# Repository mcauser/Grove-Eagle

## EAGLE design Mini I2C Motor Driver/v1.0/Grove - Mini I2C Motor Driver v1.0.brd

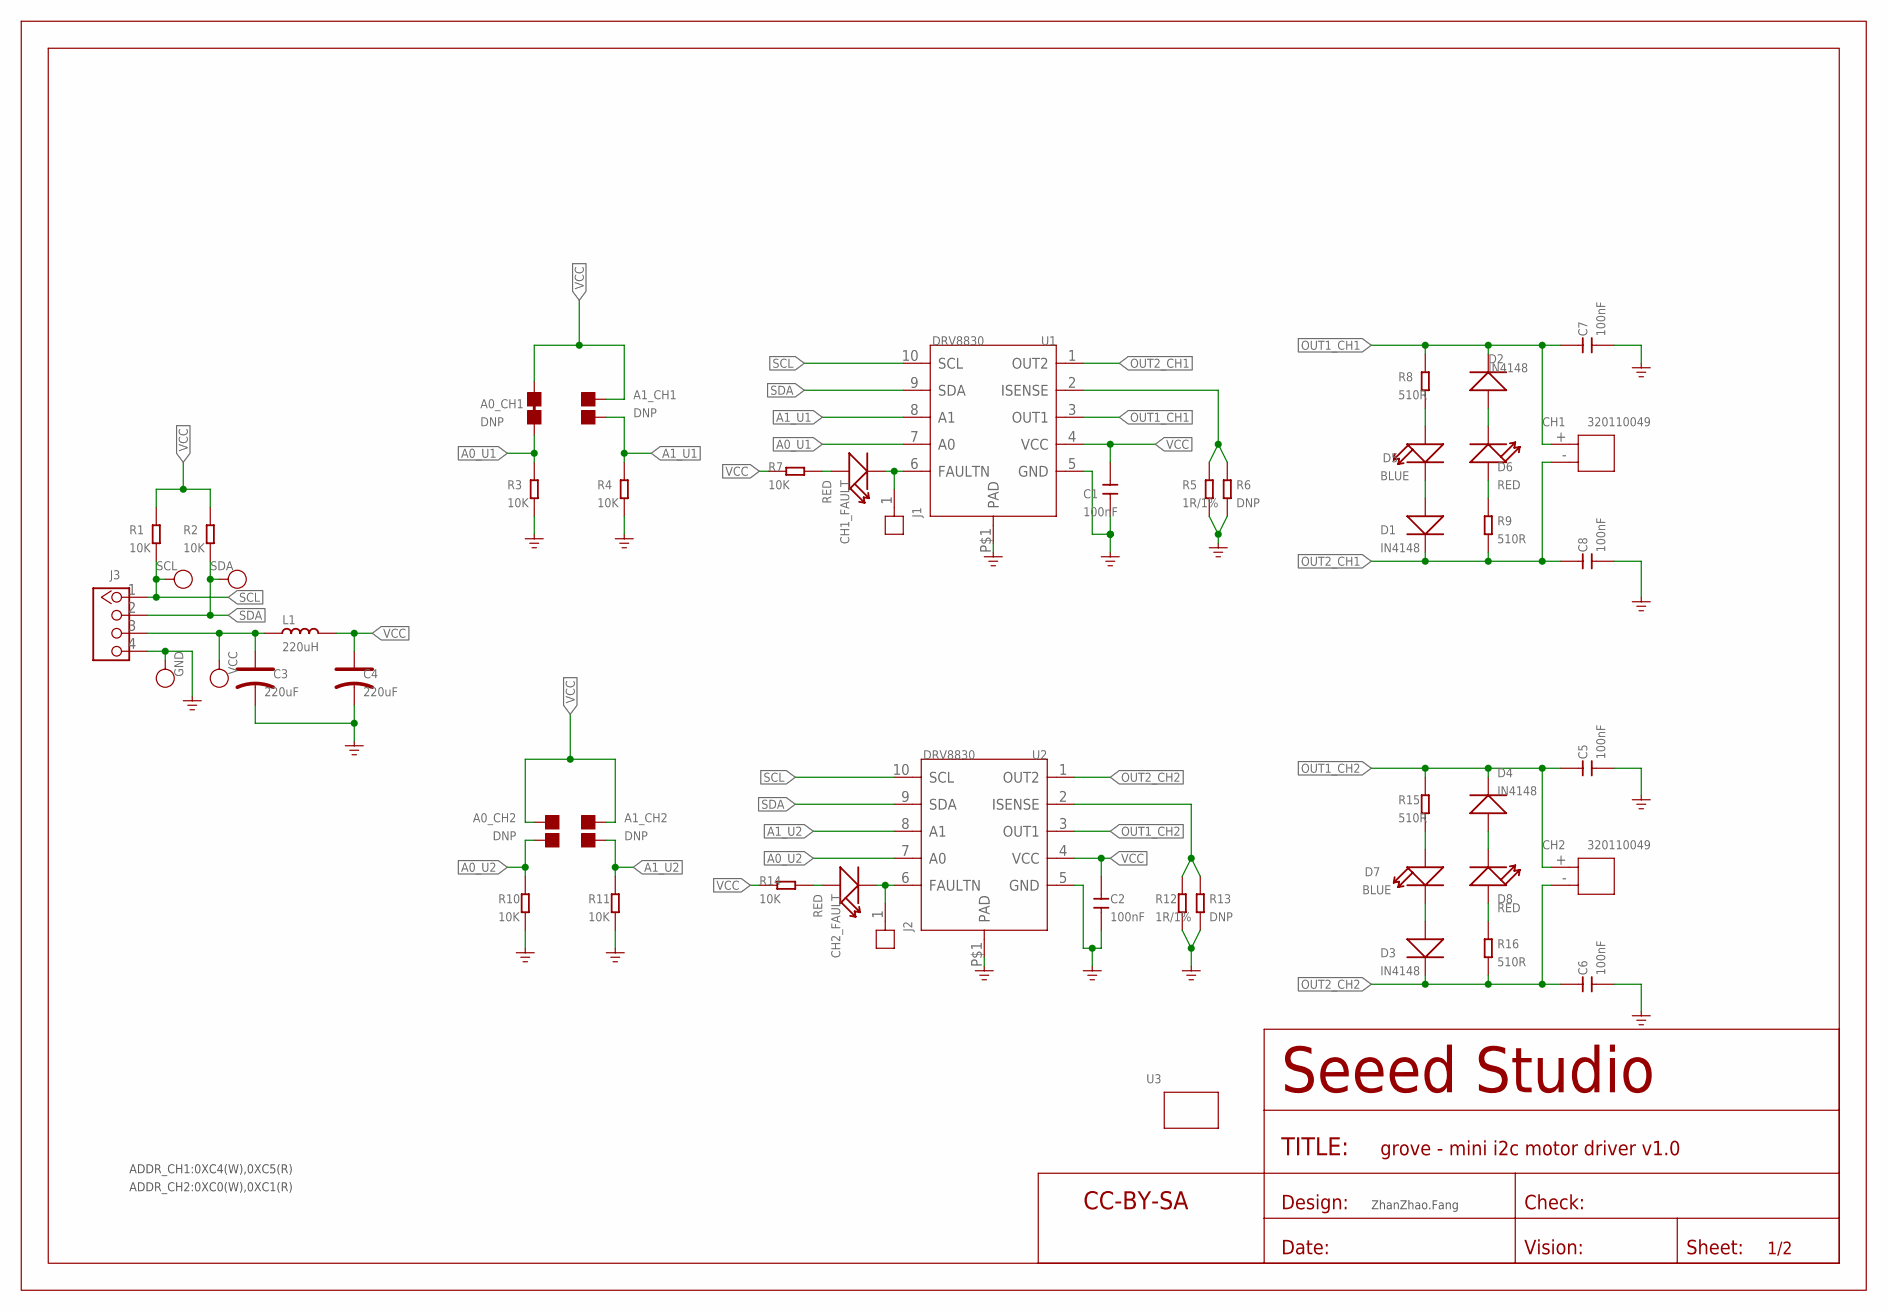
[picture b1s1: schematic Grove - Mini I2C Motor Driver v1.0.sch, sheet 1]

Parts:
A0_CH1: DNP; 2P-SMD-SHORT
A0_CH2, A1_CH1, A1_CH2: DNP; JUMPER-2P
C1, C2, C5, C6, C7, C8: 100nF; C0603
C3, C4: 220uF; AVX-B
CH1, CH2: 320110049; H2-2.0-6X4.5MM
CH1_FAULT, CH2_FAULT: RED; LED-0603
D1, D2, D3, D4: IN4148; SOD-323
D5, D7: BLUE; LED-0603
D6, D8: RED; LED-0603
GND: DNP; TP-D45MIL
J1, J2: HEADER-1P-40; 1P-80/40MIL
J3: GROVE-CONNECTOR-DIP-2.0; HW4-2.0
L1: 220uH; INT2-SMD-4.8X4.8X3MM
R1, R2, R3, R4, R7, R10, R11, R14: 10K; R0603
R5, R12: 1R/1%; R0603
R6, R13: DNP; R0603
R8, R9, R15, R16: 510R; R0603
SCL: DNP; TP-D45MIL
SDA: DNP; TP-D45MIL
U1, U2: DRV8830; MSOP10-0.5-3X3MM
U3: GROVE'2U'; GROVE-1*2-TEST-PLATFORM
U$1: SEEEDSTUDIO-OPEN-SCH-FRAME; SEEEDSTUDIO-PCB-FRAME
VCC: DNP; TP-D45MIL

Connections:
A0_U1: A0_CH1.1, R3.2, U1.7 (A0)
A0_U2: A0_CH2.1, R10.2, U2.7 (A0)
A1_U1: A1_CH1.1, R4.2, U1.8 (A1)
A1_U2: A1_CH2.1, R11.2, U2.8 (A1)
GND: C1.2, C2.2, C3.-, C4.-, C5.2, C6.2, C7.2, C8.2, GND.T, J3.4, R3.1, R4.1, R5.1, R6.1, R10.1, R11.1, R12.1, R13.1, U1.5 (GND), U1.P$1 (PAD), U2.5 (GND), U2.P$1 (PAD)
unnamed: R5.2, R6.2, U1.2 (ISENSE)
unnamed: R12.2, R13.2, U2.2 (ISENSE)
unnamed: CH1_FAULT.-, J1.1, U1.6 (FAULTN)
unnamed: CH1_FAULT.+, R7.1
unnamed: CH2_FAULT.-, J2.1, U2.6 (FAULTN)
unnamed: CH2_FAULT.+, R14.1
unnamed: D1.+, D5.-
unnamed: D6.+, R9.2
unnamed: D2.+, D6.-
unnamed: D5.+, R8.1
unnamed: D3.+, D7.-
unnamed: D7.+, R15.1
unnamed: D4.+, D8.-
unnamed: D8.+, R16.2
unnamed: C3.+, J3.3, L1.1, VCC.T
OUT1_CH1: C7.1, CH1.+, D2.-, R8.2, U1.3 (OUT1)
OUT1_CH2: C5.1, CH2.+, D4.-, R15.2, U2.3 (OUT1)
OUT2_CH1: C8.1, CH1.-, D1.-, R9.1, U1.1 (OUT2)
OUT2_CH2: C6.1, CH2.-, D3.-, R16.1, U2.1 (OUT2)
SCL: J3.1, R1.1, SCL.T, U1.10 (SCL), U2.10 (SCL)
SDA: J3.2, R2.1, SDA.T, U1.9 (SDA), U2.9 (SDA)
VCC: A0_CH1.2, A0_CH2.2, A1_CH1.2, A1_CH2.2, C1.1, C2.1, C4.+, L1.2, R1.2, R2.2, R7.2, R14.2, U1.4 (VCC), U2.4 (VCC)

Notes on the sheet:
ADDR_CH1:0XC4(W),0XC5(R)
ADDR_CH2:0XC0(W),0XC1(R)
ZhanZhao.Fang

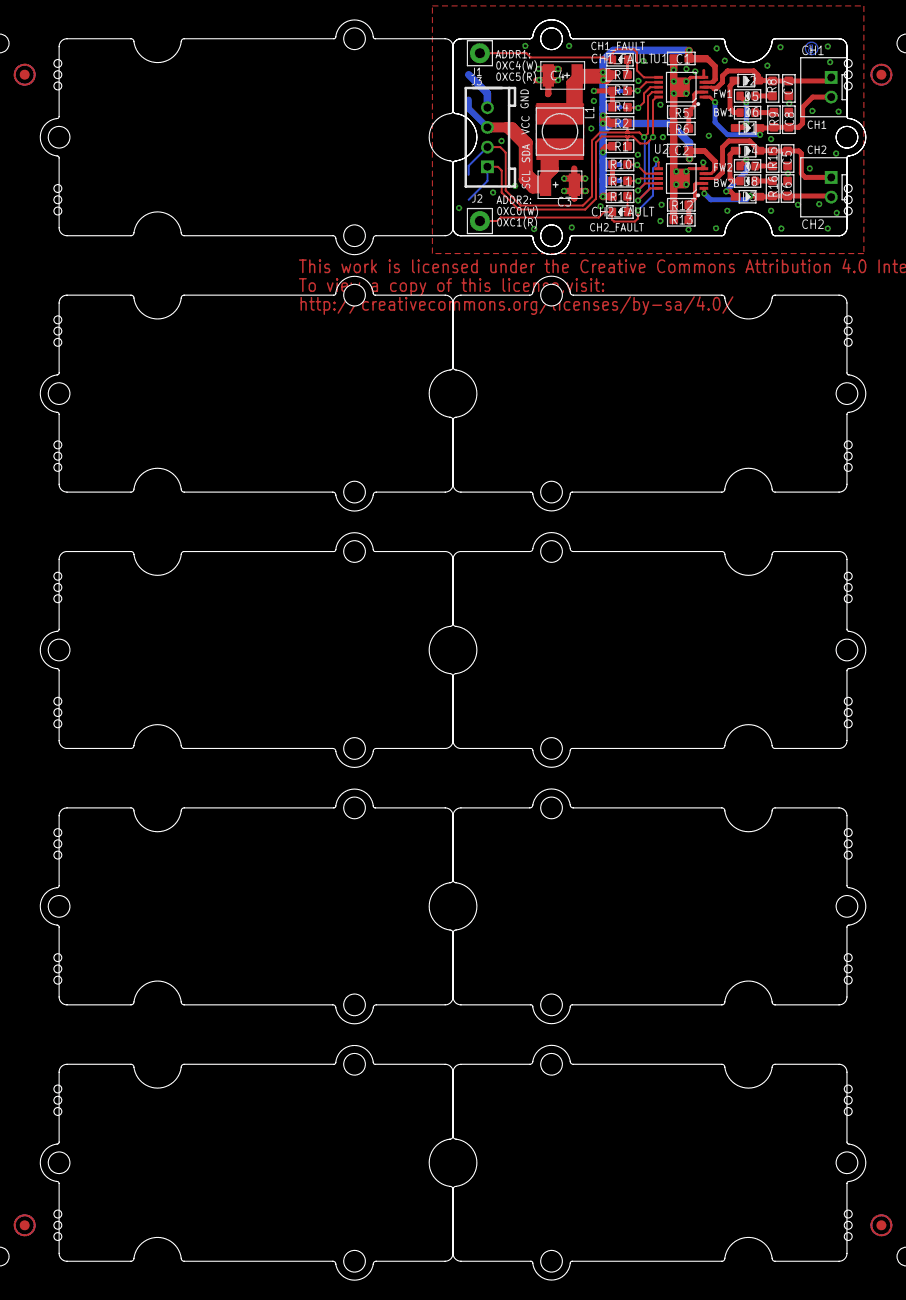
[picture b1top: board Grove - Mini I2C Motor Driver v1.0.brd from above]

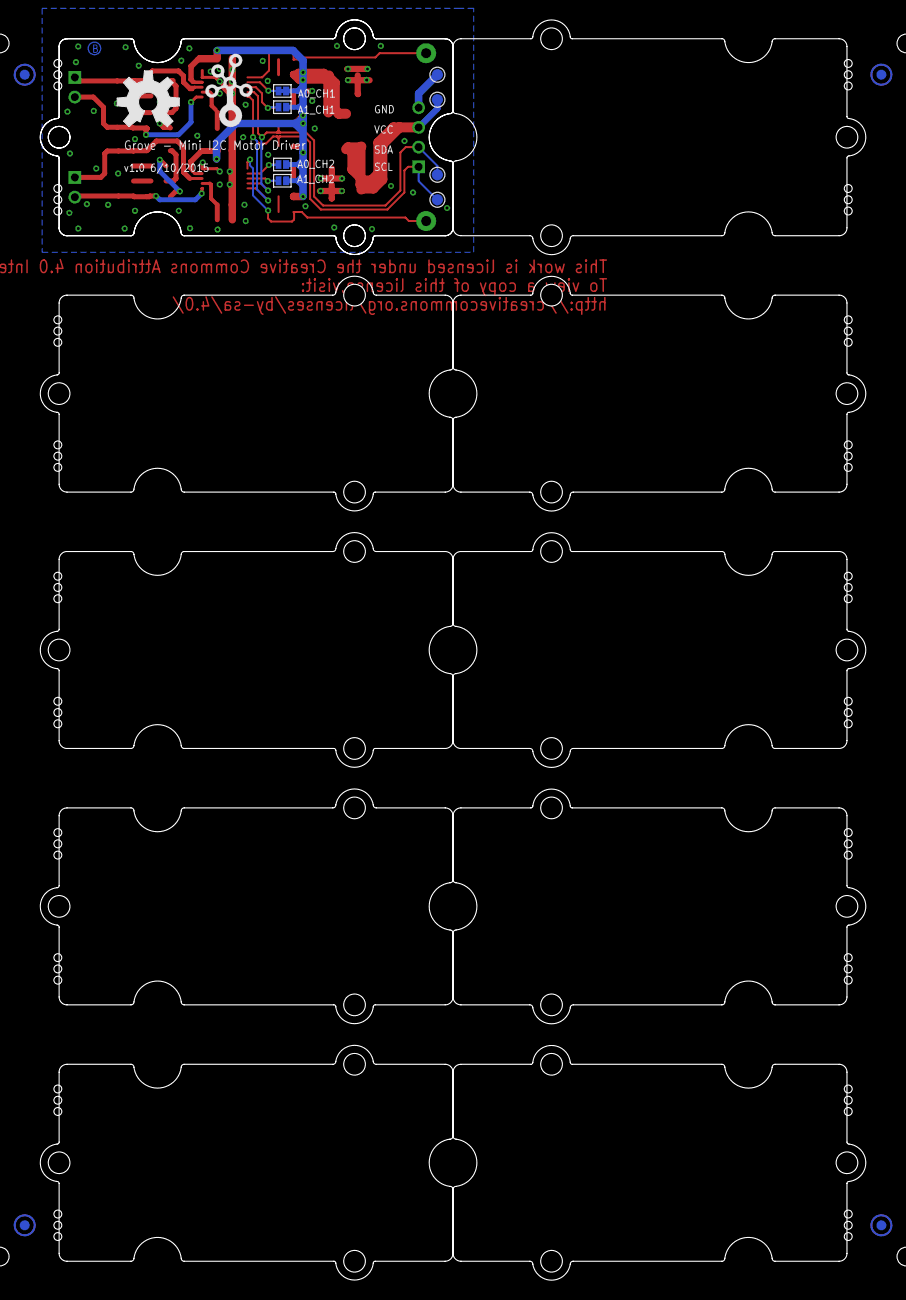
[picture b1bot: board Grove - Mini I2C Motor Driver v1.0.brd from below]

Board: 2 copper layers, 83.8 x 128.0 mm, 72 parts (14 on the bottom side), 27 nets.

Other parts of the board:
P1, P2, P3, P4, P5, P6, P7, P8: ROUND-MARK-1.0
U4, U5, U6, U7, U8, U9, U10, U11, U12, U13: GROVE-TEST-PLATFORM
U$8: OSHW_FILLX250_NOTEXT
U$14: GROVE-SILK-BIG

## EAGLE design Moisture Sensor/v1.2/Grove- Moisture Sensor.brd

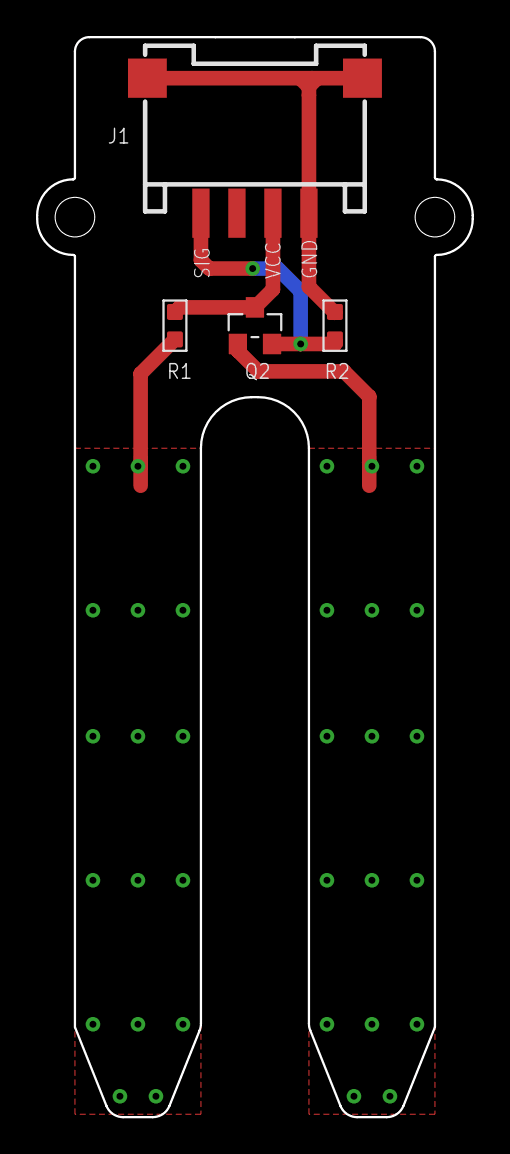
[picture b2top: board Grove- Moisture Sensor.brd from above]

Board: 2 copper layers, 24.2 x 60.0 mm, 9 parts (2 on the bottom side), 5 nets.

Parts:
J1: 4P-SMD-2.0-90D
P1, P2: 1P-SMD-0.76X0.76
Q2: SOT23
R1, R2: 100; 0603
U1: 3U-DIM-W/-DRILL-SPECIAL
U$1: LOGO-TWIG; TWIGLOGO
U$2: OSHW_FILLX200_NOTEXT

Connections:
GND: J1.4, J1.SS1, J1.SS2, R2.1
unnamed: P2.1, Q2.1
PAD_1: P1.1, R1.2
SIG: J1.1, Q2.2, R2.2
VCC: J1.3, Q2.3, R1.1

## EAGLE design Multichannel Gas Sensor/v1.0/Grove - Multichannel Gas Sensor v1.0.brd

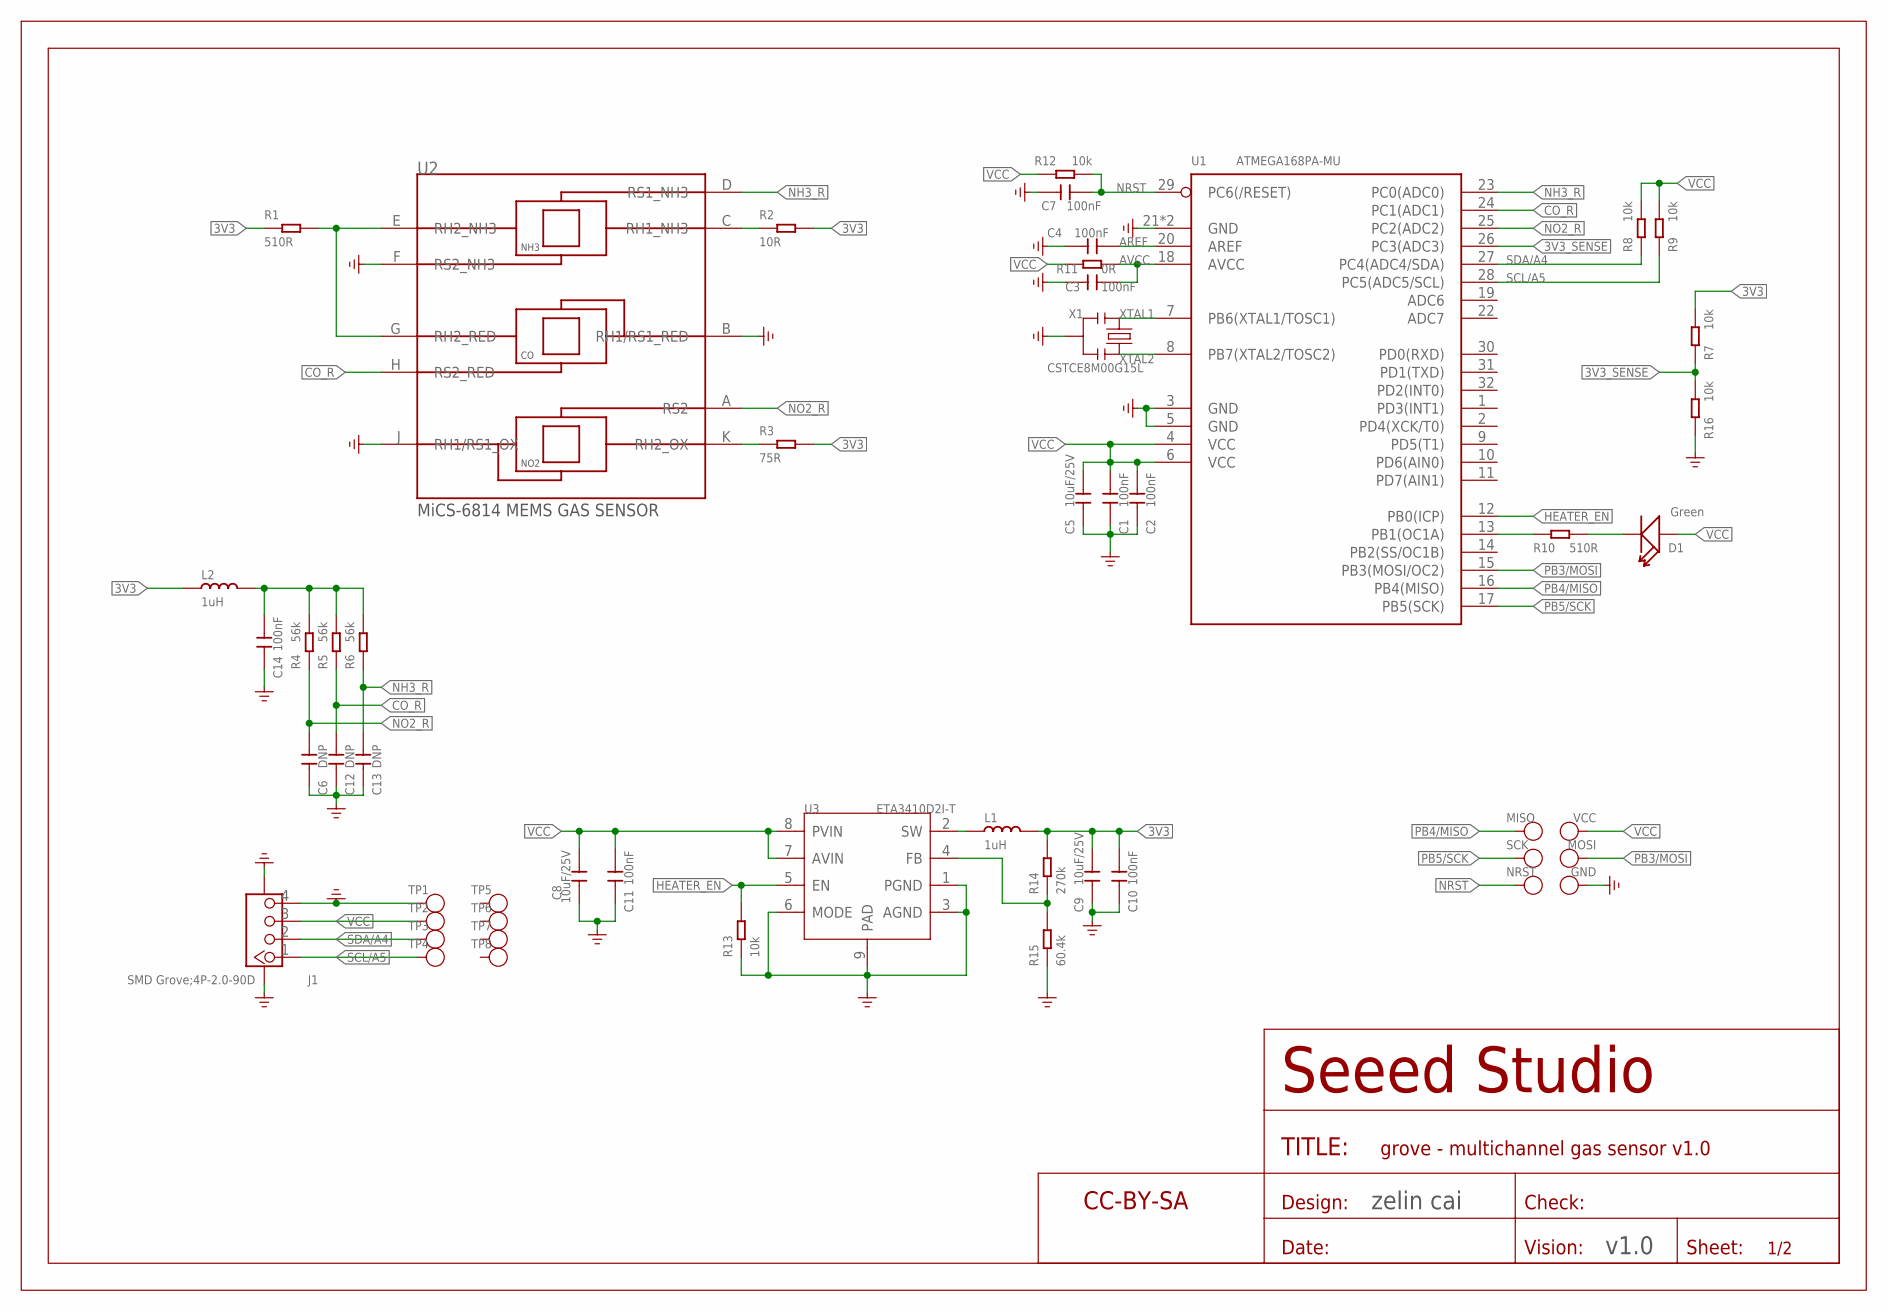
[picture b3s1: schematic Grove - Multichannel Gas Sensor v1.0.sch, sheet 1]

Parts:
C1, C2, C3, C4, C7, C10, C11, C14: 100nF; C0402
C5, C8, C9: 10uF/25V; C0805
C6, C12, C13: DNP; C0402
D1: Green; LED-0402
GND: GND; TP-D45MIL
J1: SMD Grove;4P-2.0-90D; HW4-SMD-2.0-90D
L1, L2: 1uH; L0603
MISO: MISO; TP-D45MIL
MOSI: MOSI; TP-D45MIL
NRST: NRST; TP-D45MIL
R1, R10: 510R; R0402
R2: 10R; R0402
R3: 75R; R0402
R4, R5, R6: 56k; R0402
R7, R8, R9, R12, R13, R16: 10k; R0402
R11: 0R; R0402
R14: 270k; R0402
R15: 60.4k; R0402
SCK: SCK; TP-D45MIL
TP1: GND; TP-D45MIL
TP2: VCC; TP-D45MIL
TP3: SDA; TP-D45MIL
TP4: SCL; TP-D45MIL
TP5, TP6, TP7, TP8: NC; TP-D45MIL
U1: ATMEGA168PA-MU; QFN32G-0.5-5X5MM
U2: MiCS-6814; MICS-6814
U3: ETA3410D2I-T; DFN8G-0.5-2X2MM
U$1: Xadow-Multichanel Gas Sensor; SEEEDSTUDIO-PCB-FRAME
VCC: VCC; TP-D45MIL
X1: CSTCE8M00G15L; RESONATOR3-SMD-3.6X1.3X0.8MM

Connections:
3V3: C9.2, C10.2, L1.2, L2.1, R1.1, R2.2, R3.2, R7.1, R14.2
3V3_SENSE: R7.2, R16.1, U1.26 (PC3(ADC3))
AREF: C4.2, U1.20 (AREF)
AVCC: C3.2, R11.2, U1.18 (AVCC)
CO_R: C12.2, R5.1, U1.24 (PC1(ADC1)), U2.H (RS2_RED)
GND: C1.1, C2.1, C3.1, C4.1, C5.1, C6.1, C7.2, C8.1, C9.1, C10.1, C11.1, C12.1, C13.1, C14.1, GND.T, J1.4, J1.SS1, J1.SS2, R13.1, R15.1, R16.2, TP1.T, U1.3 (GND), U1.5 (GND), U1.21 (GND), U1.33 (GND), U2.B (RH1/RS1_RED), U2.F (RS2_NH3), U2.J (RH1/RS1_OX), U3.1 (PGND), U3.3 (AGND), U3.6 (MODE), U3.9 (PAD), X1.2
HEATER_EN: R13.2, U1.12 (PB0(ICP)), U3.5 (EN)
unnamed: R1.2, U2.E (RH2_NH3), U2.G (RH2_RED)
unnamed: R2.1, U2.C (RH1_NH3)
unnamed: R10.1, U1.13 (PB1(OC1A))
unnamed: R3.1, U2.K (RH2_OX)
unnamed: D1.-, R10.2
unnamed: C14.2, L2.2, R4.2, R5.2, R6.2
unnamed: L1.1, U3.2 (SW)
unnamed: R14.1, R15.2, U3.4 (FB)
NH3_R: C13.2, R6.1, U1.23 (PC0(ADC0)), U2.D (RS1_NH3)
NO2_R: C6.2, R4.1, U1.25 (PC2(ADC2)), U2.A (RS2)
NRST: C7.1, NRST.T, R12.1, U1.29 (PC6(/RESET))
PB3/MOSI: MOSI.T, U1.15 (PB3(MOSI/OC2))
PB4/MISO: MISO.T, U1.16 (PB4(MISO))
PB5/SCK: SCK.T, U1.17 (PB5(SCK))
SCL/A5: J1.1, R9.2, TP4.T, U1.28 (PC5(ADC5/SCL))
SDA/A4: J1.2, R8.2, TP3.T, U1.27 (PC4(ADC4/SDA))
VCC: C1.2, C2.2, C5.2, C8.2, C11.2, D1.+, J1.3, R8.1, R9.1, R11.1, R12.2, TP2.T, U1.4 (VCC), U1.6 (VCC), U3.7 (AVIN), U3.8 (PVIN), VCC.T
XTAL1: U1.7 (PB6(XTAL1/TOSC1)), X1.1
XTAL2: U1.8 (PB7(XTAL2/TOSC2)), X1.3

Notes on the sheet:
zelin cai
v1.0

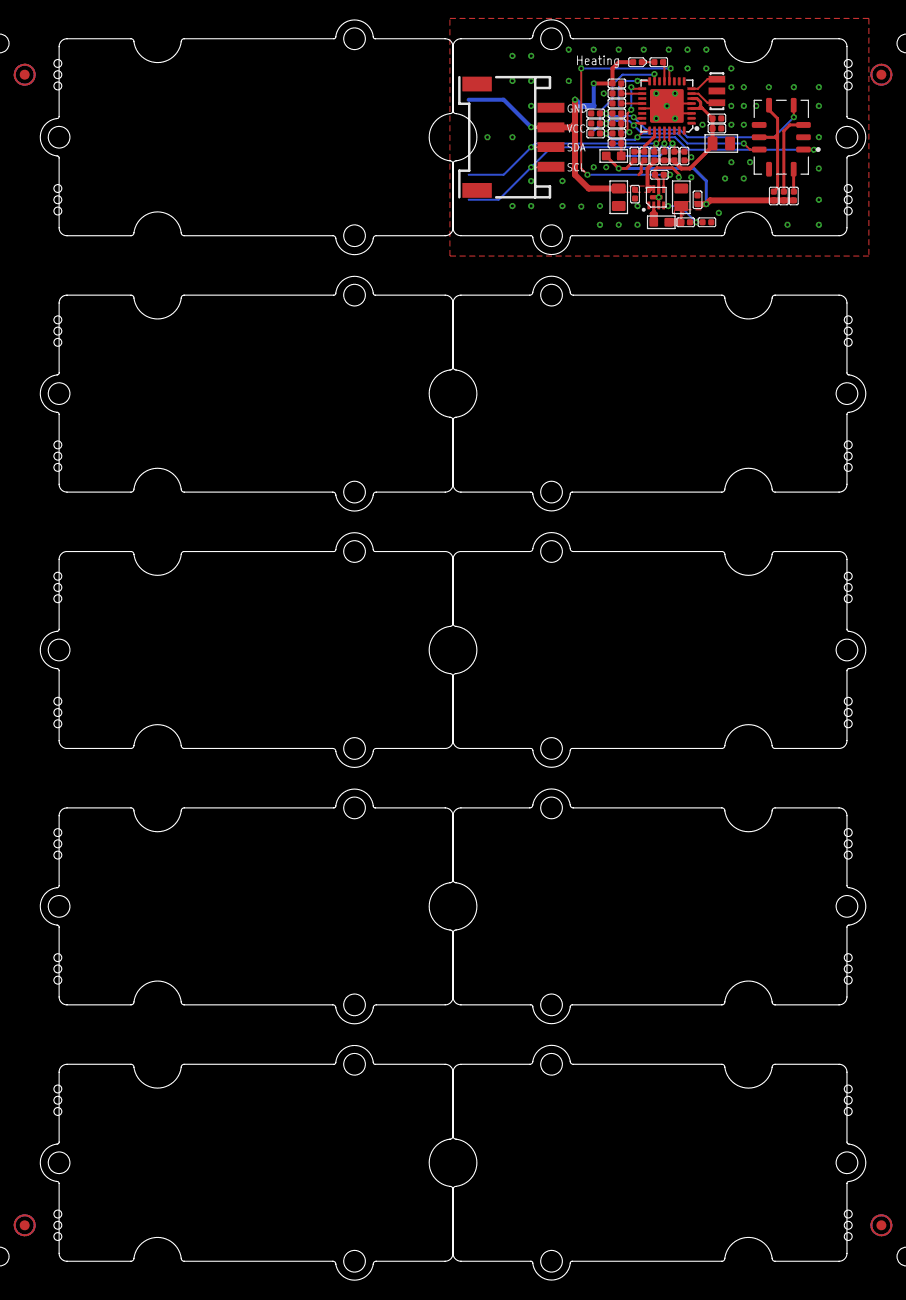
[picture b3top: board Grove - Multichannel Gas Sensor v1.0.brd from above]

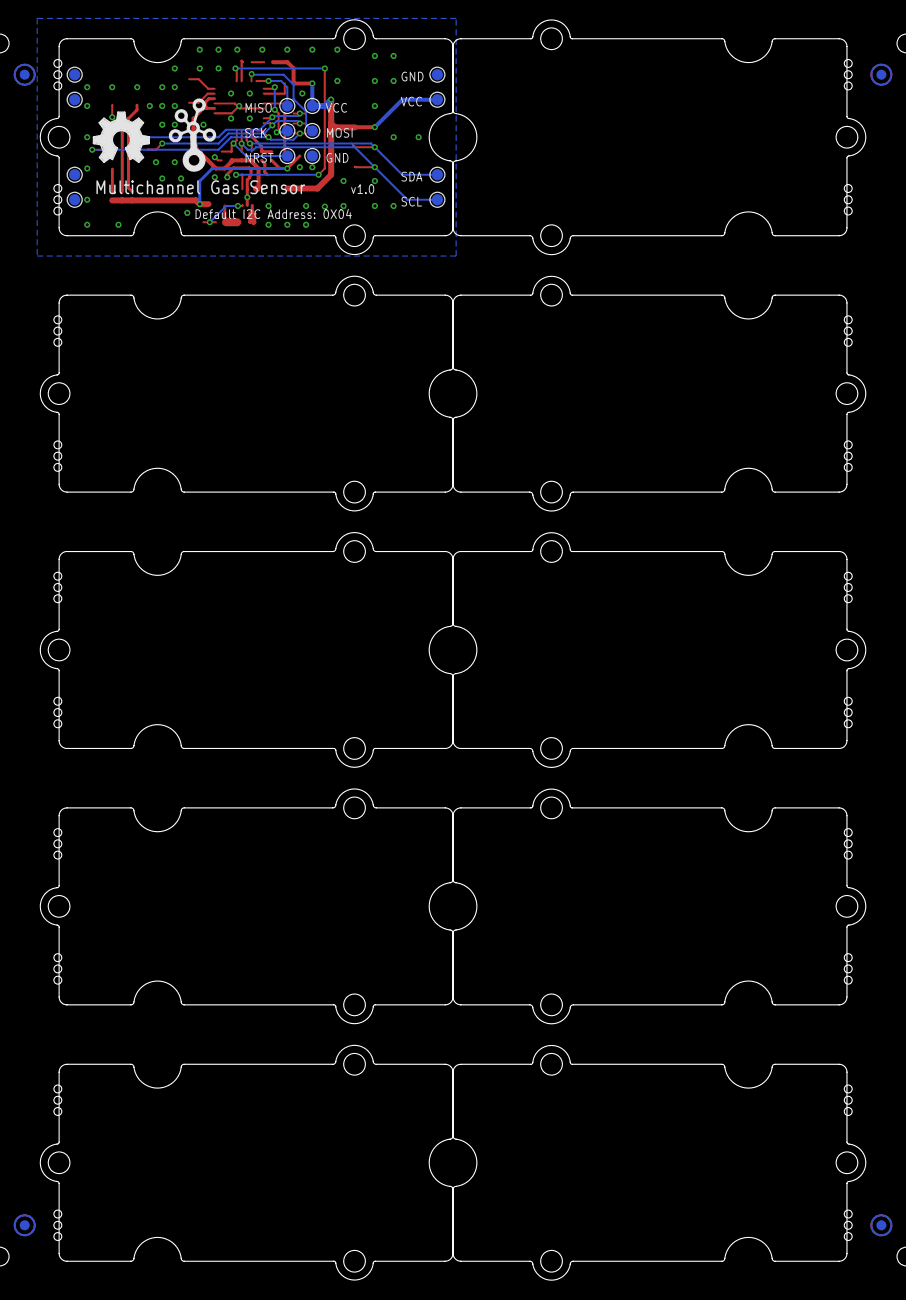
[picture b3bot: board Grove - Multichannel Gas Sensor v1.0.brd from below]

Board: 2 copper layers, 83.8 x 128.0 mm, 73 parts (20 on the bottom side), 26 nets.

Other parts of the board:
P1, P2, P3, P4, P5, P6, P7, P8: ROUND-MARK-1.0
U4, U5, U6, U7, U8, U9, U10, U12, U13: GROVE-TEST-PLATFORM
U$23: GROVE-1*2-TEST-PLATFORM
U$24: OSHW_FILLX200_NOTEXT
U$25: GROVE-SILK-BIG

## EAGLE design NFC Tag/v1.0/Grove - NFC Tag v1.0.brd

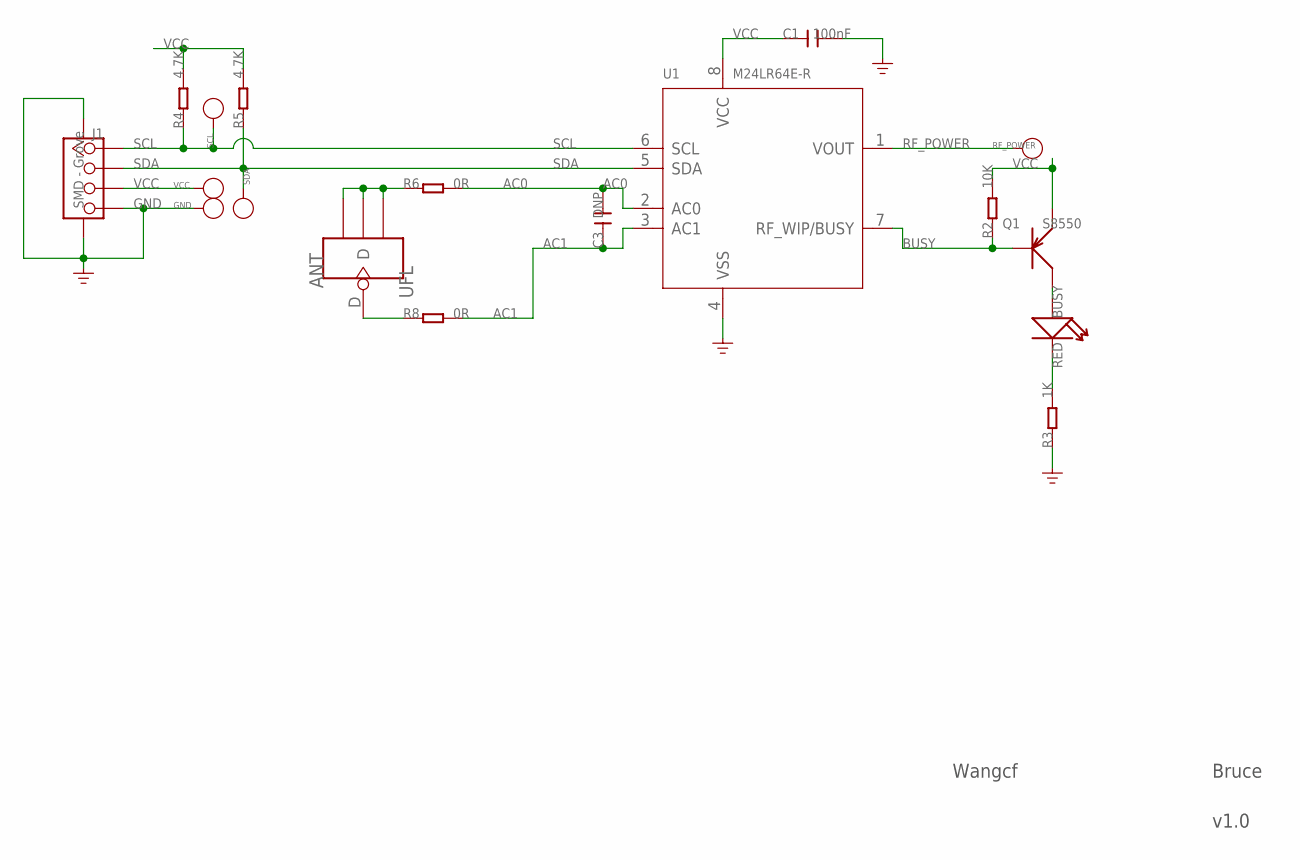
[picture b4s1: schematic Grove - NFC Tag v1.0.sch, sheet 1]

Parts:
ANT: UFL; 4P-U-FL
BUSY: RED; LED-0603
C1: 100nF; C0402
C3: DNP; C0402
GND: PAD-TEST-POINT'4545'; TP_4545
J1: SMD - Grove; 4P-SMD-2.0
Q1: S8550; SOT23
R2: 10K; R0402
R3: 1K; R0402
R4, R5: 4.7K; R0402
R6, R8: 0R; R0402
RF_POWER: PAD-TEST-POINT'4545'; TP_4545
SCL: PAD-TEST-POINT'4545'; TP_4545
SDA: PAD-TEST-POINT'4545'; TP_4545
U1: M24LR64E-R; TSSOP8
VCC: PAD-TEST-POINT'4545'; TP_4545

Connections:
AC0: C3.2, R6.2, U1.2 (AC0)
AC1: C3.1, R8.2, U1.3 (AC1)
BUSY: Q1.1 (B), R2.1, U1.7 (RF_WIP/BUSY)
GND: C1.2, GND.T, J1.4, J1.SS1, J1.SS2, R3.1, U1.4 (VSS)
unnamed: BUSY.+, Q1.3 (C)
unnamed: BUSY.-, R3.2
unnamed: ANT.D, R8.1
unnamed: ANT.GND1, ANT.GND2, ANT.GND3, R6.1
RF_POWER: RF_POWER.T, U1.1 (VOUT)
SCL: J1.1, R4.1, SCL.T, U1.6 (SCL)
SDA: J1.2, R5.1, SDA.T, U1.5 (SDA)
VCC: C1.1, J1.3, Q1.2 (E), R2.2, R4.2, R5.2, U1.8 (VCC), VCC.T

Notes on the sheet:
Wangcf
Bruce
v1.0

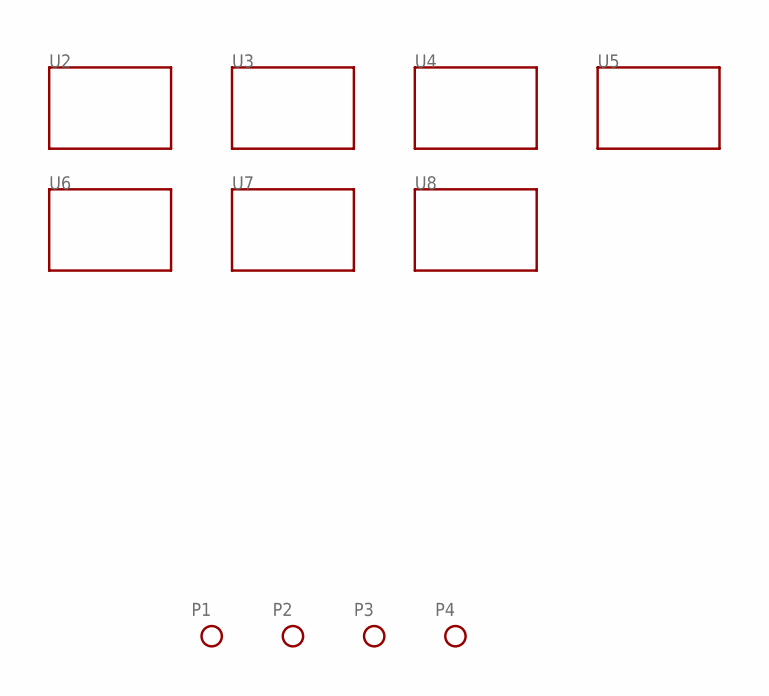
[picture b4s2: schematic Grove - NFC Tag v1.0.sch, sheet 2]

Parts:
P1, P2, P3, P4: PAD-MARK; ROUND-MARK-1.0
U2, U3, U4, U5, U6, U7, U8: TWIG'2U'; GROVE-TEST-PLATFORM

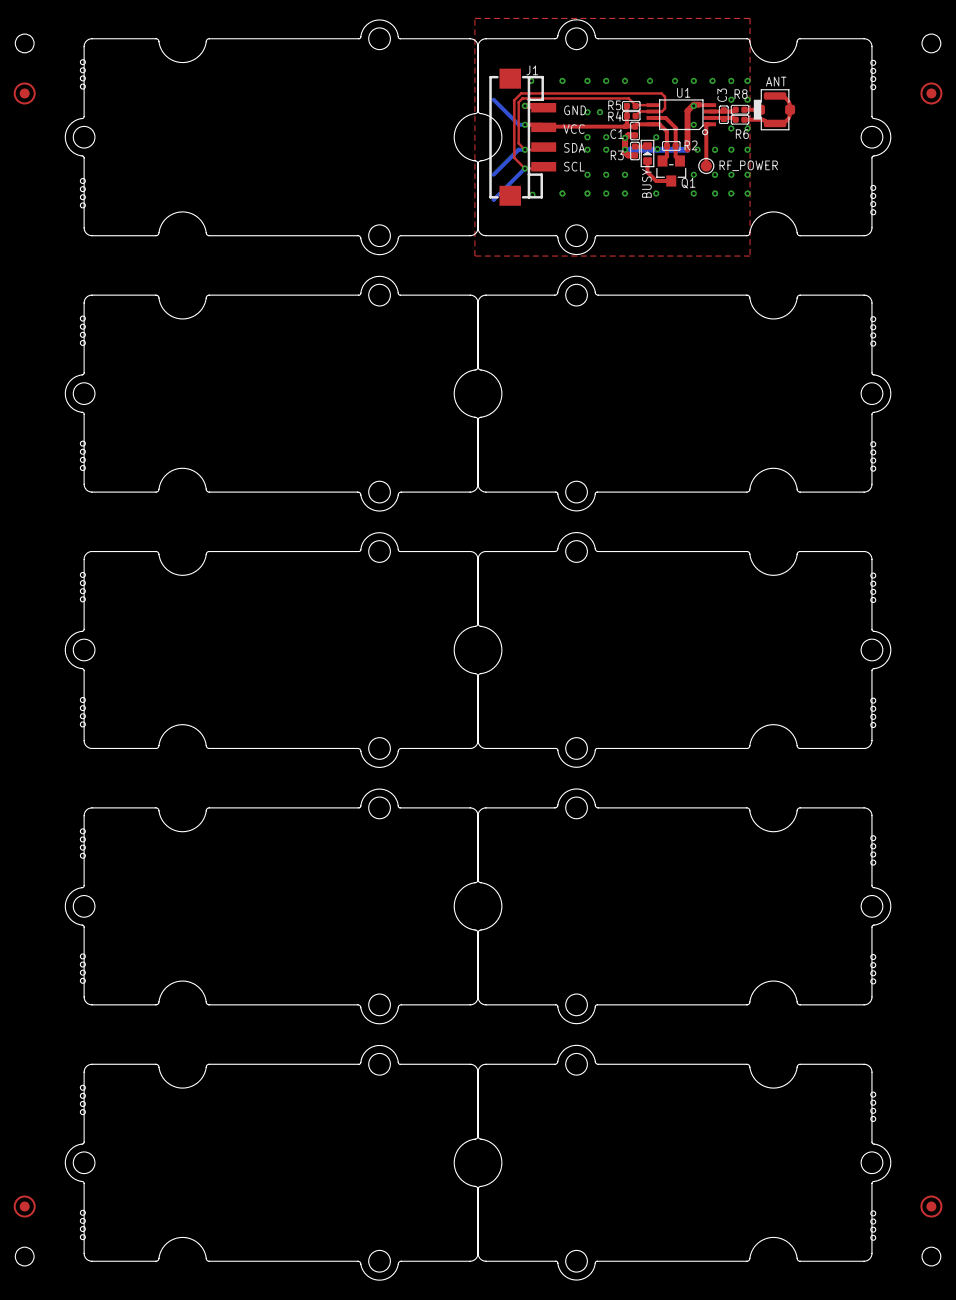
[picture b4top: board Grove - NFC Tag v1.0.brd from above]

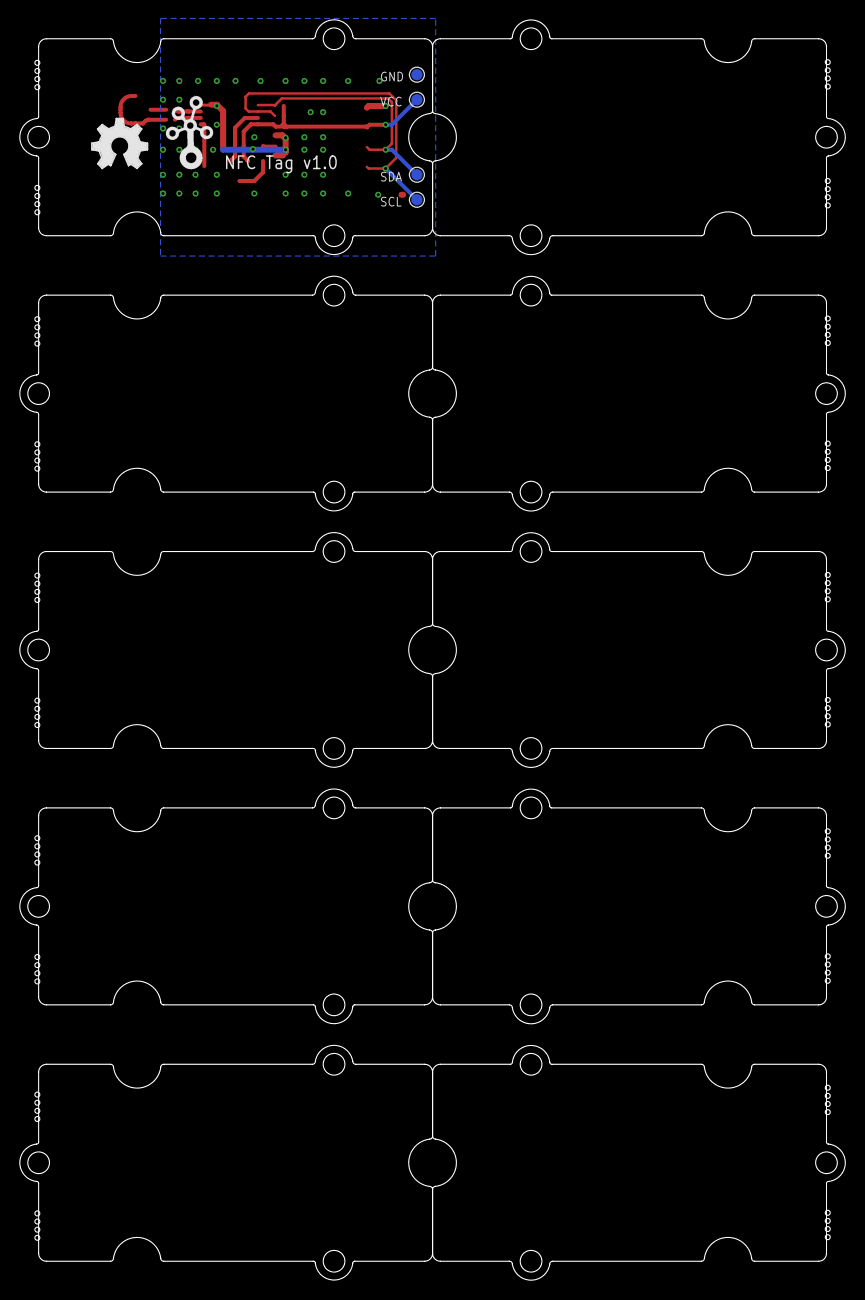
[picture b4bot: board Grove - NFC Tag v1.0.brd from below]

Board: 2 copper layers, 83.8 x 128.0 mm, 34 parts (6 on the bottom side), 12 nets.

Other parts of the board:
U10, U11: GROVE-TEST-PLATFORM
U$4: OSHW_FILLX200_NOTEXT
U$5: GROVE-2CONNECTOR-SMD
U$6: TWIGLOGO

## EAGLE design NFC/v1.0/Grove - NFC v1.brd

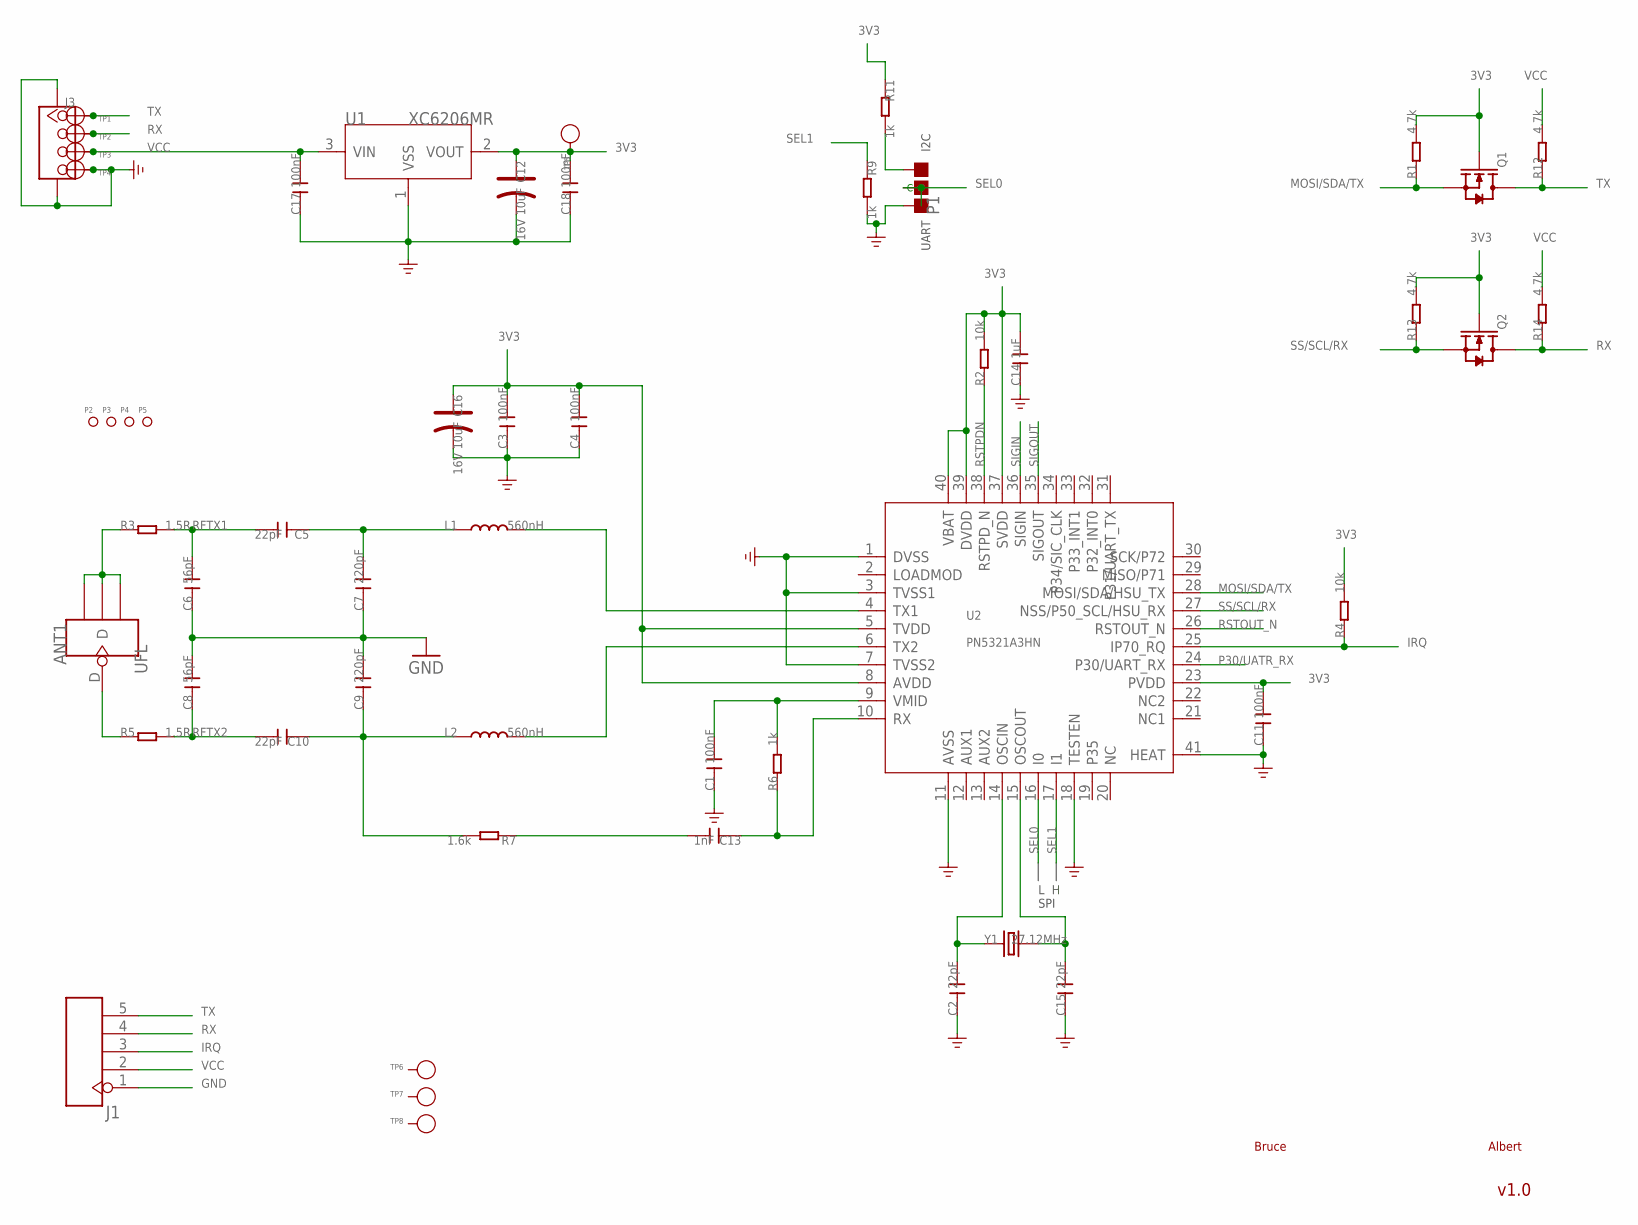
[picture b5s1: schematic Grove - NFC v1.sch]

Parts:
ANT1: UFL; 4P-U-FL
C1, C3, C4, C11, C17, C18: 100nF; C0402
C2, C5, C10, C15: 22pF; C0402
C6, C8: 56pF; C0402
C7, C9: 220pF; C0402
C12, C16: 16V 10uF; AVX-A
C13: 1nF; C0402
C14: 1uF; C0603
J1: HEADER-5P-2.54; 5P-2.54
J3: TWIG-4P-2.0-SMD-FEMALE-REINFORCE'90D'; 4P-SMD-2.0-90D
L1, L2: 560nH; L0603
P1: PAD-JUMPER-3P-40*40; 3P-SMD-4.1X1.5
P2, P3, P4, P5: PAD-MARK; ROUND-MARK-1.0
Q1, Q2: MOSFET-N'SOT23'; SOT23
R1, R12, R13, R14: 4.7k; R0402
R2, R4: 10k; R0402
R3, R5: 1.5R; R0402
R6, R9, R11: 1k; R0402
R7: 1.6k; R0402
TP1, TP2, TP3, TP4, TP5, TP6, TP7, TP8: PAD-TEST-POINT'4545'; TP_4545
U1: XC6206MR; SOT23
U2: PN5321A3HN; HVQFN40
Y1: 27.12MHz; 4P-SMD-3.2X2.5

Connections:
3V3: C3.2, C4.2, C11.2, C12.+, C14.2, C16.+, C18.2, Q1.1 (G), Q2.1 (G), R1.2, R2.2, R4.2, R11.1, R13.2, TP5.T, U1.2 (VOUT), U2.5 (TVDD), U2.8 (AVDD), U2.23 (PVDD), U2.37 (SVDD), U2.39 (DVDD), U2.40 (VBAT)
GND: C1.1, C2.1, C3.1, C4.1, C6.1, C7.1, C8.2, C9.2, C11.1, C12.-, C14.1, C15.1, C16.-, C17.1, C18.1, J1.1, J3.4, J3.SS1, J3.SS2, P1.11 (R), R9.2, TP4.T, U1.1 (VSS), U2.1 (DVSS), U2.3 (TVSS1), U2.7 (TVSS2), U2.11 (AVSS), U2.18 (TESTEN), U2.41 (HEAT)
IRQ: J1.3, R4.1, U2.25 (IP70_RQ)
MOSI/SDA/TX: Q1.2 (S), R1.1, U2.28 (MOSI/SDA/HSU_TX)
unnamed: C2.2, U2.14 (OSCIN), Y1.2 (1)
unnamed: C15.2, U2.15 (OSCOUT), Y1.4 (2)
unnamed: L2.2, U2.6 (TX2)
unnamed: L1.2, U2.4 (TX1)
unnamed: C5.1, C7.2, L1.1
unnamed: C13.2, R7.1
unnamed: C9.1, C10.1, L2.1, R7.2
unnamed: ANT1.GND1, ANT1.GND2, ANT1.GND3, R3.1
unnamed: C1.2, R6.2, U2.9 (VMID)
unnamed: P1.00 (L), R11.2
unnamed: C13.1, R6.1, U2.10 (RX)
unnamed: ANT1.D, R5.1
P30/UATR_RX: U2.24 (P30/UART_RX)
RFTX1: C5.2, C6.2, R3.2
RFTX2: C8.1, C10.2, R5.2
RSTOUT_N: U2.26 (RSTOUT_N)
RSTPDN: R2.1, U2.38 (RSTPD_N)
RX: J1.4, J3.2, Q2.3 (D), R14.1, TP2.T
SEL0: P1.MM (C), U2.16 (I0)
SEL1: R9.1, U2.17 (I1)
SIGIN: U2.36 (SIGIN)
SIGOUT: U2.35 (SIGOUT)
SS/SCL/RX: Q2.2 (S), R13.1, U2.27 (NSS/P50_SCL/HSU_RX)
TX: J1.5, J3.1, Q1.3 (D), R12.1, TP1.T
VCC: C17.2, J1.2, J3.3, R12.2, R14.2, TP3.T, U1.3 (VIN)

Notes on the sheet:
v1.0
SPI
Bruce
Albert
I2C
UART

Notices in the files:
parts and their libraries:
moudle-new: This work is licensed under the Creative Commons Attribution 4.0 International License.
To view a copy of this license,visit:
http://creativecommons.org/licenses/by-sa/4.0
moudle-new: CC-BY-SA
